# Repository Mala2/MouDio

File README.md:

<p align="center">

	  <br/>
  	<a href="https://discord.gg/jvKunuGb8d">

<p align="center">
🚨 ⚠ This project is currently still under development ⚠️ 🚨

<p align="center">

<p align="center">
(https://www.MouDio.net)
</p>

# Overview
Introducing the fully functional Bluetooth Speaker, featuring modern design and high-performance capabilities. With the choice of ATmega328P or ESP32 microcontroller at its core and compatibility with Arduino & Platformio, this portable speaker offers easy construction, allowing users to quickly and easily set it up, and the high-quality audio ensures that your music will sound great.

The speaker also boasts the Qualcomm® CSR8675 FSC-BT806 and 2x Texas Instruments® TAS5825M amplifiers, providing low distortion and powerful output of 2 x 30 W.

The PCB prototypes have been built and tested, with excellent results. The hardware design is complete, and we are now focusing on the software development. We invite you to explore the shared files for more information on this exciting project.

[*🎨 View on FUSION 360*](https://a360.co/3Bk0sSi)
<p align="center">

# Features
	
* **Amplifier** - 2x  Texas Instruments® [*TAS5825M*](https://www.ti.com/product/TAS5825M) Which has low distortion can output 2x 30 W, 2.2 Mode (8-Ω, 24 V, THD+N=1%)
* **Connectivity** - The [*FSC-BT806 Feasycom*](https://github.com/Mala2/FSC-BT806) features
 Qualcomm® **CSR8675** - **Bluetooth V5.0** Support HSP, HFP, A2DP, AVRCP, PBAP,MAP,SPP,BLE profile - Coverage up to 15m - 2 microphone inputs - **Audio interfaces:** I²S/PCM and SPDIF

* **Power** - Accept **USB C IN** Delivery **Up to 2.5A  Charge Current**  - **USB A OUT** Capable of **10W-5V,2A** - **Low idle power** consumption - **7500mAh** battery capacity upgradeable to **15000mAh**

* **Arduino IDE Programmable Bluetooth-Speaker**
<p align="center">

 # Repository Contents

👩‍🚀 **[3D Files ](3D-Files)** • The **Bluetooth-Speaker** components in many formats (probably what you are looking for to 3d print)

🔉 **[Hardware](Hardware)** • The internal PCBs files (Gerber, Schematic)

💻 **[Software](Software)** • Codes and Libraries for use with the **MouDio**

📄 **[Documentation](Documentation)** • Datasheets, other references

🎲 **[Prototype](Prototype)** • Evaluation board, Cases, etc.

<p align="center">

# Block Diagram

The following displays the latest Block Diagram; Things may change, and probably there may be some discrepancy between the schematic and the block diagram.

<p align="center">

# Schematics

The following displays the ****[TOP Main](Documentation/TOP-Main/)**** PCB. It contain the Atmega328|ESP32 uC, LED Driver, Haptic Driver, RTC, Touch Sensor (TPR54|48), EEPROM*, Supervisory, Addressable LEDs

****[V1](Hardware/TOP/)****
	
[📐 *View on FUSION 360*](https://a360.co/3VPY0L3)

<p align="center">

The following displays the ****[BACK Charger](Documentation/BACK-Charger/)**** PCB.It contain MAX77961 3S Charger, MAX17320 Fuel Gauge, MAX25231ATCA 5V Buck, MAX77503BEWC33 3V3 Buck, 3S Battery.

****[V1](Hardware/BACK/)****
	
[📐 *View on FUSION 360*](https://a360.co/3UELmh8)
	
<p align="center">

The following displays the ****[BOTTOM Amplifier](Documentation/BOTTOM-Amplifier/)**** PCB.It contain the Amplifier - 2x Texas Instruments® TAS5825M and The FSC-BT806 Feasycom Bluetooth Moduel.

****[V1](Hardware/BOTTOM/)****	
	
[📐 *View on FUSION 360*](https://a360.co/3FziKBq)

<p align="center">

The following displays the ****[FRONT Speaker](Documentation/FRONT-Speaker/)**** PCB.To hold the Speakers and front acrylic grill

****[V1](Hardware/FRONT/)****
	
[📐 *View on FUSION 360*](https://a360.co/3BfI0KE)

<p align="center">

# Working Principal

**1. First, I am going to use the TPR54 Touch Sensor Modules to turn ON/OFF the system, if pin [I/O-2] "TAP" it is pressed >2s. This module can send  active High signal output to the ATmega328p pin 2 [INT0].**

**2. After waking up, the ATmega328 will send a high signal to turn on the Bluetooth Module BT-806 through pin [8] "Vreg" and the TAS5825 circuitry through pin [A3] "PDN".**

🔸	**Startup Procedures: [I/O_2] "TAP" pressed for >2s**

*	The ATmega328p wakes up upon High signal on pin 2 [INT0].

*	Send a 3V3 high signal to haptic driver to enable the IC.

*       initialize the LED driver IS31FL3195 to wakeup.

*	Turn on the haptic driver as an indication for 1s.

*	Turn on the LED driver to play a motion from left to right as wake up inication.

*	Turn on the LED driver to reflect the current SOC% of the battery with the help of the fuel gauge MAX17320 and check whether the charger is presnt or not set the LEDs accordingly. 

*	Send a 3V3 high signal of more than 100ms to Bluetooth Module BT-806 through VREG_IN (PLAY/PAUSE) pin to boot the module, then bring the signal back to low.

*	Once power supplies are stable, bring up PDN of TAS5825 to High and wait 5ms.

*	Set the Amplifier TAS5825 into the HiZ state and enable DSP via the I2C control port.

*	Wait 5ms at least. Then initialize the DSP Coefficient, then set the TAS5825 to Play state.

*       initialize the charger MAX77961.

	<br />
	
🔸	**Shutdown Procedures: [I/O_2] "TAP" pressed for >2s**

*	Configure the Register 0x03h -D[1:0]=10 (Hiz) via the I2C control port and Pull PDN low.

*	Wait at least 6ms (this time depends on the LRCLK rate, digital volume, and digital volume ramp-down rate).

*	Send a 3V3 high signal of more than 100ms to Bluetooth Module BT-806 through VREG_IN (PLAY/PAUSE) pin to turn off the module, then bring the signal back to low.

*	The ATmega328 goes to deep sleep, waiting for the next event.
	
	<br />

🔸	**Charging Procedures:**

*	Once the charge input is present, the MAX77961 will send an interrupter either through INTB, INOKB pins

*	Turn on the haptic driver as an indication for 1s.

*	Display the current SOC% with 4 LEDs with the help of an LED driver as long as the charge input is present. Otherwaise, the ATmega328 goes to deep sleep, waiting for the next event.

<br />
	
**3. Once the speaker is ON, the TPR54 is responsible for interacting with Bluetooth Module BT-806 to change the song and volume. (Keep in mind that the TAS5825 can also change just the volume) through TX/RX UART pin between the ATmega328 and Bluetooth Module BT-806 at 115200 rate data. For example: Once the ATmega328 is connected to BT-806, It can send a command to change the volume. For example,**

**And so on. Also, if the BAT SOC% is low, alert the user with an LED blinking and start the Shutdown Procedures once the BAT is too low to operate the system > 15%.**

# To Do List

♦️ **Need help with software part.**

1- After making sure the BT806 is OFF through the commands AT+, Turns the BT806 after turning the 3v3. Sending a high signal to Vreg for > 2s upon waking up, then remain Low. (OR MOSFET NETWORK)
	
2- If the battery is < 15%, shut down the speaker if no charging is present.
			     
✅ 3- If the battery is <35%, set the MAX volume to be less than 70%. In other words, it reduces the volume to not consume more power. TAS5825 has register 0x4c and 0x54 (AGAIN or DIGITAL_VOL) to set that.

4- (after checking the vol range of bt806), send a command AT+SPKVOL and check the volume range of BT806 sent. After that, set the TAS5825 accordingly; that can be done with two registers, either 0x4c and 0x54 (AGAIN or DIGITAL_VOL).
	
✅ 5- For example, once the user swap to the right (Next Song). The LEDs should indicate that from left to right emotions.

6- If no sounds or connection is established for 30 min, turn off the speaker. Either by checking the current flow from the fuel gauge MAX17320 or the BT-806 is not in play status or the TAS5825 register 0x03 is mute status for more than 30 min.

✅ 7- If the charger is inserted, activate the haptic driver as feedback.

9- If the charger is inserted, increase the volume range to be even higher as more power will be provided. This can be done if the 0x4C register is changed accordingly with the attached and disattached of the charger.

10- Add resetFunc() after touching the middle TAP more than 10s.

11- Get the header file for the TAS5825M to act as Dual stereo 2.2 and output the best sounds. You need PPC3 software and hardware access to test the setup and extract the best DSP settings.

12- Create the initialization code configuring the bq28z610 fuel gauge to work with the Arduino Uno and create a Library, and also create a “control” object for the bq28z610 fuel gauge. This includes configuring the IC’s registers via I2C to set configurations. In addition, looking to expose all features of the target ICs in code so that a user can easily configure those features using variables.

♦️ TO BE CONTINUED
	<p align="center">
     
# Components

🔷 **Speakers**

<p align="center">

[*ND65-8 2-1/2"*](https://www.parts-express.com/Dayton-Audio-ND65-8-2-1-2-Aluminum-Cone-Full-Range-Driver-8-290-206?gclid=CjwKCAjwkvWKBhB4EiwA-GHjFrtrRhF_nZh4KP2HR51msc4nOYF4FvnND1y967XQK91w8MbXJw41TxoC_Y0QAvD_BwE) **X2**

🔷 **Tweeters**

<p align="center">

[*ND20FA-6 3/4"*](https://www.parts-express.com/Dayton-Audio-ND20FA-6-3-4-Soft-Dome-Neodymium-Tweeter-275-030?quantity=1&custcol1=Dayton%20Audio%20ND20FA-6%203%2F4%22%20Soft%20Dome%20Neodymium%20Tweeter&custcol_ava_item=275-030&custcol_ava_incomeaccount=General&custcol_ava_upccode=844632000874&custcol_ava_pickup=F&custcol_disableshopping=F) **X2**

🔷 **Acousta-Stuf Polyfill**

<p align="center">

[*Acousta-Stuf Polyfill*](https://www.parts-express.com/Acousta-Stuf-Polyfill-1-lb.-Bag-260-317?quantity=1&custcol1=Acousta-Stuf%20Polyfill%201%20lb.%20Bag&custcol_ava_item=260-317&custcol_ava_incomeaccount=General&custcol_ava_upccode=844632037382&custcol_ava_pickup=F&custcol_disableshopping=F)

🔷 **Brass Threaded Metal**
M3 3mm M3-0.5 Brass Threaded Metal Heat Set Screw Inserts for 3D Printing

<p align="center">

[*Brass Threaded Metal*](https://www.ebay.com/itm/292174792941)

🔷 **Silicone Rubber Mat 60x8x3mm**

<p align="center">

[*Silicone Rubber Mat*](https://www.aliexpress.com/item/3256801841973589.html?spm=a2g0o.order_list.0.0.21ef1802Ng4OPe&gatewayAdapt=4itemAdapt)**X2**

<p align="center">

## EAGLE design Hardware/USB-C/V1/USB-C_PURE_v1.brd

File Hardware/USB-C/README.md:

[📐 *View on FUSION 360*](https://a360.co/3fcBBV4)

FRONT
-------------------

BACK
-------------------

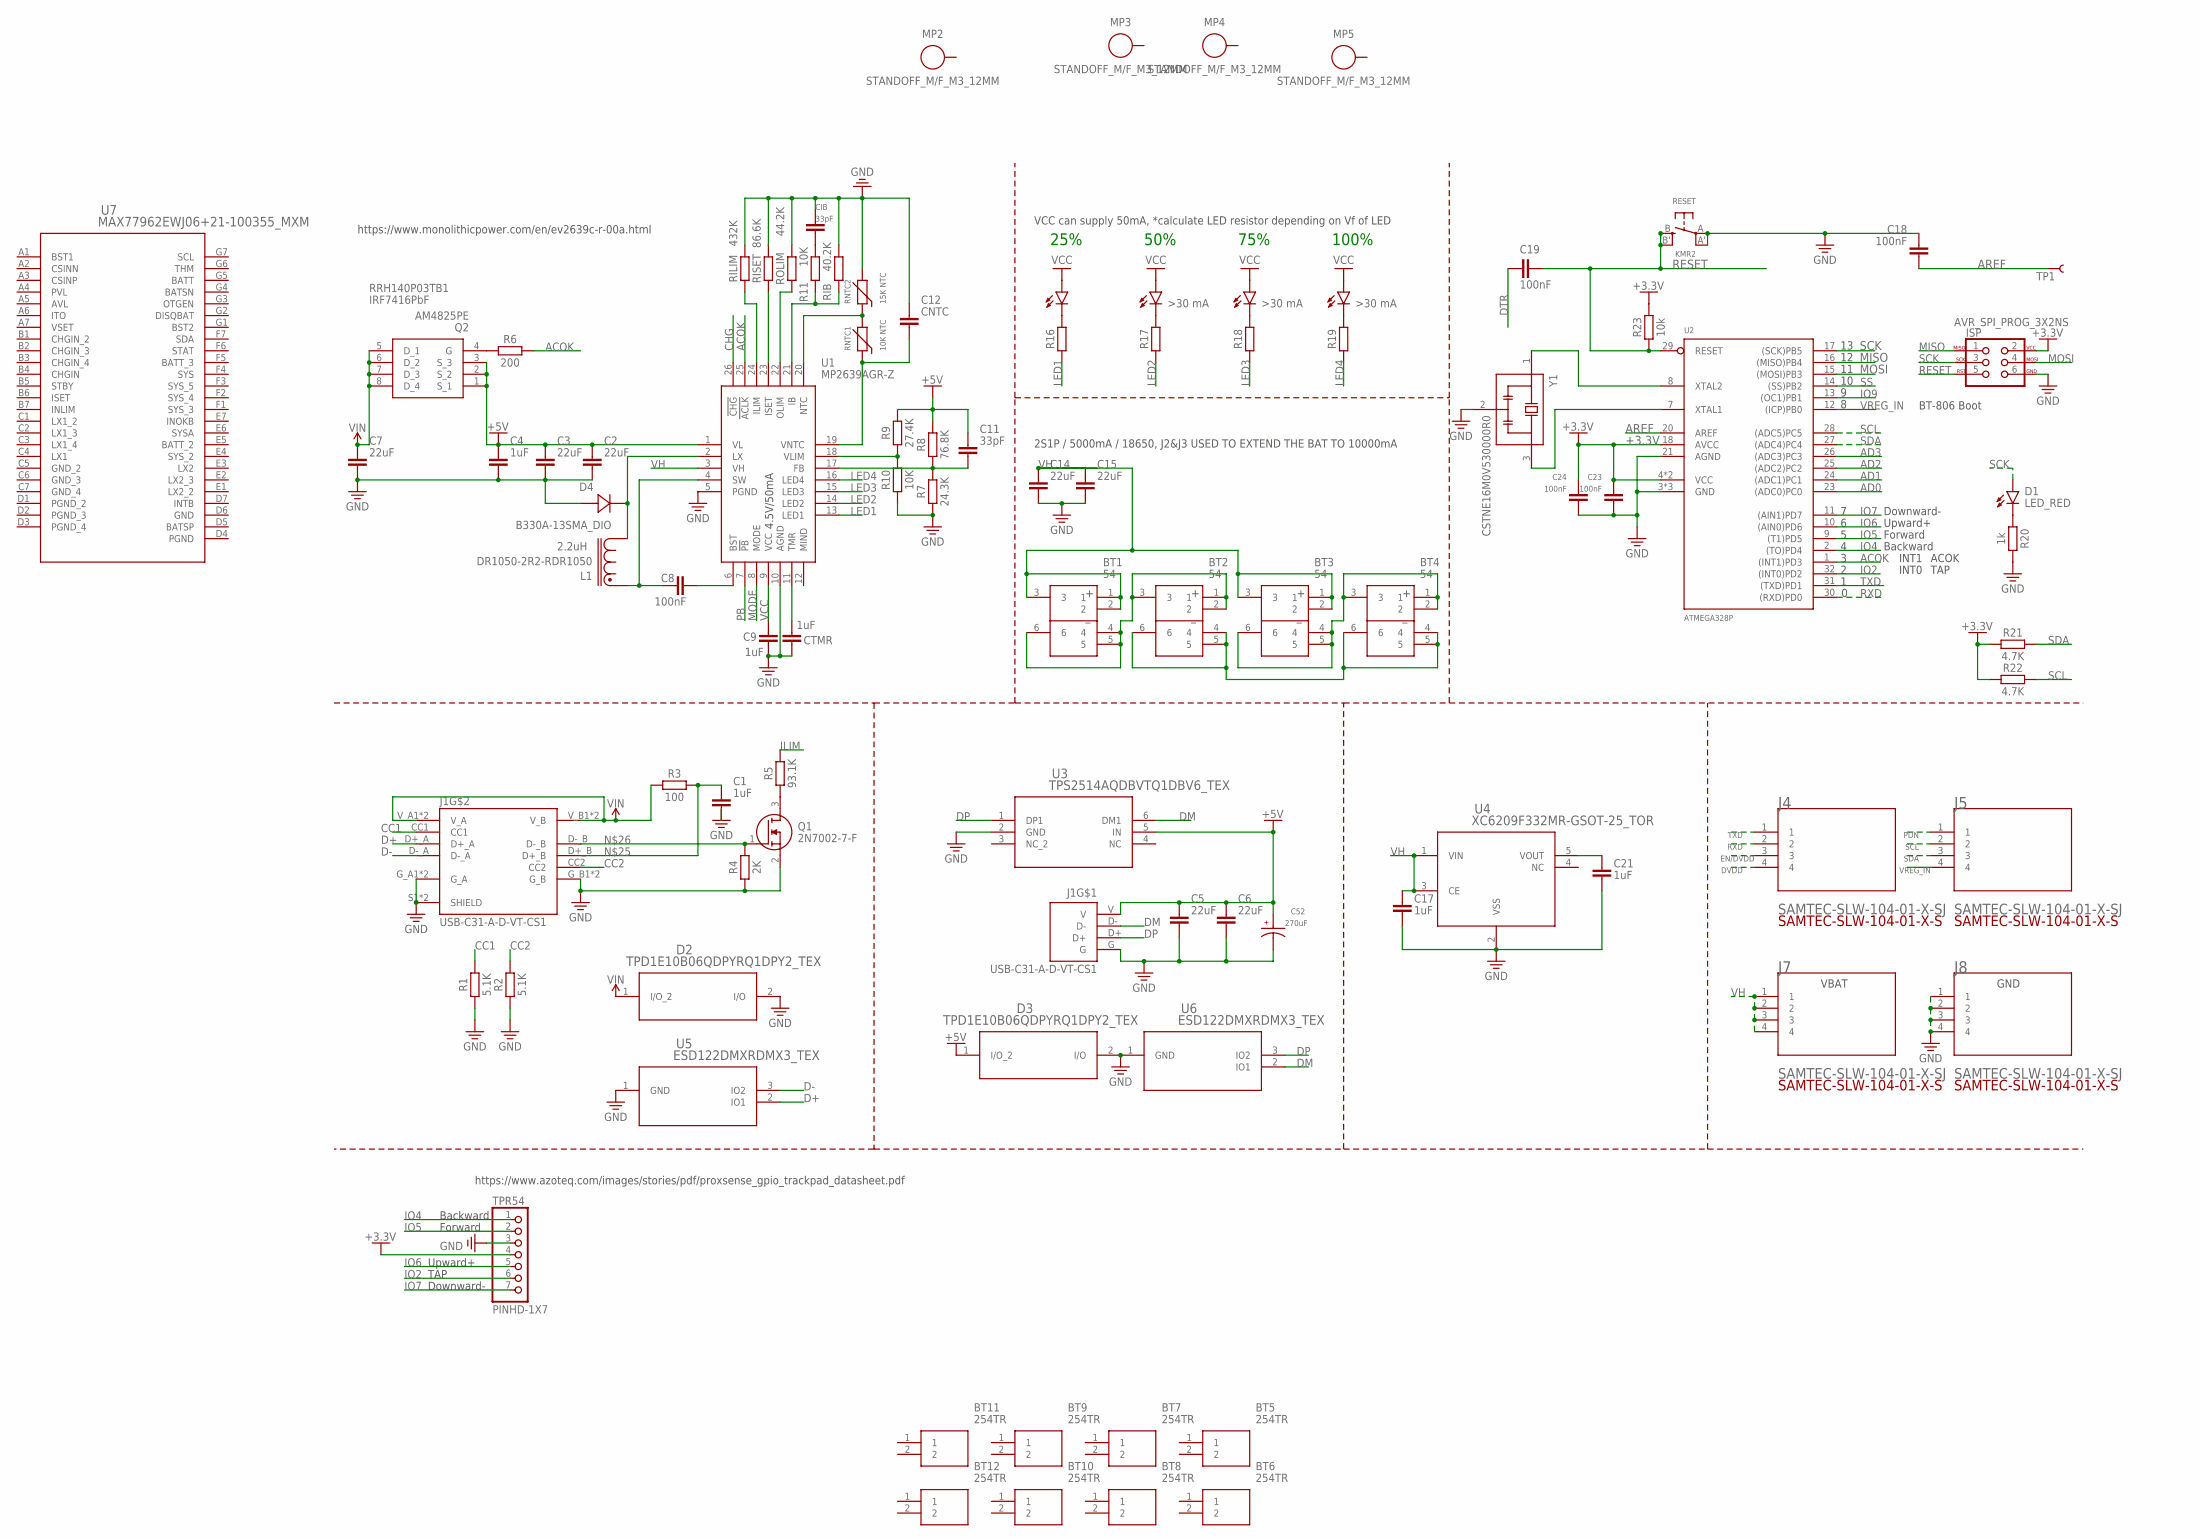
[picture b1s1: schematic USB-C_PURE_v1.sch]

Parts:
BT1, BT2, BT3, BT4: 54
BT5, BT6, BT7, BT8, BT9, BT10, BT11, BT12: 254TR
C1, C4, C9, C17, C21: 1uF; CAPC2012X110
C2, C3, C5, C6, C7, C14, C15: 22uF; CAPC2012X110
C8, C18, C19, C23, C24: 100nF; CAPC1005X60
C11: 33pF; CAPC1005X60
C12: CNTC; CAPC1005X60
C52: 270uF; CAP_16SVPG270M
CIB: 33pF; CAPC1005X60
CTMR: 1uF; CAPC2012X110
D1: LED_RED; LEDC2012X105N_RND-R
D2, D3: TPD1E10B06QDPYRQ1DPY2_TEX; DPY2_TEX
D4: B330A-13SMA_DIO; SMA_DIO
ISP: AVR_SPI_PROG_3X2NS; 2X3-NS
J1: USB-C31-A-D-VT-CS1; ADAMTECH_USB-C31-A-D-VT-CS1
J4, J5, J7, J8: SAMTEC-SLW-104-01-X-SJ; SAMTEC-SLW-104-01-X-S
L1: DR1050-2R2-RDR1050; DR1050
LED1: AA2810
LED2, LED3, LED4: EAPL3809WA1
MP2, MP3, MP4, MP5: STANDOFF_M/F_M3_12MM; STANDOFF_HEX_MALE-FEMALE_550X1200_M3X0.5_MTGP850H320
Q1: 2N7002-7-F; SOT96P240X120-3N
Q2: AM4825PE; SOIC127P600X175-8N
R1, R2: 5.1K; RESC1005X40
R3: 100; RESC1005X40
R4: 2K; RESC1005X40
R5: 93.1K; RESC1005X40
R6: 200; RESC1005X40
R7: 24.3K; RESC1005X40
R8: 76.8K; RESC1005X40
R9: 27.4K; RESC1005X40
R10, R11: 10K; RESC1005X40
R16, R17, R18, R19: R_CHIP-0402(1005-METRIC); RESC1005X40
R20: 1k; RESC1005X40
R21, R22: 4.7K; RESC1005X40
R23: 10k; RESC1005X40
RESET: KMR2; BTN_KMR2_4.6X2.8
RIB: 40.2K; RESC1005X40
RILIM: 432K; RESC1005X40
RISET: 86.6K; RESC1005X40
RNTC1: 10K NTC; THRMC1608X60N
RNTC2: 15K NTC; THRMC1608X60N
ROLIM: 44.2K; RESC1005X40
TP1: TEST-POINT3; PAD.03X.03
TPR54: PINHD-1X7; 1X07
U1: MP2639AGR-Z; MP2639AGRZ
U2: ATMEGA328P; MLF32-TH
U3: TPS2514AQDBVTQ1DBV6_TEX; DBV6_TEX
U4: XC6209F332MR-GSOT-25_TOR; SOT-25_TOR
U5, U6: ESD122DMXRDMX3_TEX; DMX3_TEX
U7: MAX77962EWJ06+21-100355_MXM; 21-100355_MXM
Y1: CSTNE16M0V530000R0; OSC_CSTNE16M0V530000R0

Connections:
+3.3V: C23.1, C24.1, ISP.2, R21.1, R22.1, R23.2, TPR54.4, U2.4 (VCC), U2.6 (VCC), U2.18 (AVCC)
+5V: C2.1, C3.1, C4.1, C5.1, C6.1, C11.1, C52.1, D3.1 (I/O_2), J1.V, Q2.1 (S_1), Q2.2 (S_2), Q2.3 (S_3), R8.2, R9.2, U1.1 (VL), U3.5 (IN)
ACOK: R6.2, U1.25 (!ACLK), U2.1 ((INT1)PD3)
AD0: U2.23 ((ADC0)PC0)
AD1: U2.24 ((ADC1)PC1)
AD2: U2.25 ((ADC2)PC2)
AD3: U2.26 ((ADC3)PC3)
AREF: C18.2, TP1.P$1, U2.20 (AREF)
CC1: J1.CC1, R1.2
CC2: J1.CC2, R2.2
CHG: U1.26 (!CHG)
D+: J1.D+_A, U5.2 (IO1)
D-: J1.D-_A, U5.3 (IO2)
DM: J1.D-, U3.6 (DM1), U6.2 (IO1)
DP: J1.D+, U3.1 (DP1), U6.3 (IO2)
DTR: C19.1
DVDD: J4.4
EN/DVDD: J4.3
GND: C1.2, C2.2, C3.2, C4.2, C5.2, C6.2, C7.2, C9.2, C12.1, C14.2, C15.2, C17.2, C18.1, C21.2, C23.2, C24.2, C52.2, CIB.1, CTMR.1, D2.2 (I/O), D3.2 (I/O), D4.2, ISP.6, J1.G, J1.G_A1 (G_A), J1.G_A2 (G_A), J1.G_B1 (G_B), J1.G_B2 (G_B), J1.S1 (SHIELD), J1.S2 (SHIELD), J8.1, J8.2, J8.3, J8.4, Q1.2 (S), R1.1, R2.1, R4.1, R7.1, R10.1, R20.2, RESET.A, RESET.A' (P1), RIB.2, RILIM.2, RISET.2, RNTC2.2, ROLIM.2, TPR54.3, U1.5 (PGND), U1.10 (AGND), U2.3 (GND), U2.5 (GND), U2.21 (AGND), U2.TH (GND), U3.2 (GND), U4.2 (VSS), U5.1 (GND), U6.1 (GND), U7.D6 (GND), Y1.2 (GND)
GND_2: U7.C5 (GND_2)
GND_3: U7.C6 (GND_3)
GND_4: U7.C7 (GND_4)
ILIM: R5.2
IO2: TPR54.6, U2.32 ((INT0)PD2)
IO4: TPR54.1, U2.2 ((TO)PD4)
IO5: TPR54.2, U2.9 ((T1)PD5)
IO6: TPR54.5, U2.10 ((AIN0)PD6)
IO7: TPR54.7, U2.11 ((AIN1)PD7)
IO9: U2.13 ((OC1)PB1)
LED1: R16.1, U1.13 (LED1)
LED2: R17.1, U1.14 (LED2)
LED3: R18.1, U1.15 (LED3)
LED4: R19.1, U1.16 (LED4)
MISO: ISP.1, U2.16 ((MISO)PB4)
MODE: U1.8 (MODE)
MOSI: ISP.4, U2.15 ((MOSI)PB3)
unnamed: Q2.4 (G), R6.1
unnamed: BT1.4, BT1.5, BT1.6, BT2.1, BT2.2, BT2.3
unnamed: Q1.3 (D), R5.1
unnamed: BT3.4, BT3.5, BT3.6, BT4.1, BT4.2, BT4.3
unnamed: LED2.- (C), R17.2
unnamed: LED1.- (C), R16.2
unnamed: C8.1, L1.1, U1.4 (SW)
unnamed: D4.1, L1.2, U1.2 (LX)
unnamed: C8.2, U1.6 (BST)
unnamed: CTMR.2, U1.11 (TMR)
unnamed: C11.2, R7.2, R8.1, U1.17 (FB)
unnamed: R9.1, R10.2, U1.18 (VLIM)
unnamed: RNTC1.2, RNTC2.1, U1.20 (NTC)
unnamed: C12.2, RNTC1.1, U1.19 (VNTC)
unnamed: RILIM.1, U1.24 (ILIM)
unnamed: RISET.1, U1.23 (ISET)
unnamed: ROLIM.1, U1.22 (OLIM)
unnamed: CIB.2, R11.2
unnamed: R11.1, RIB.1, U1.21 (IB)
unnamed: LED3.- (C), R18.2
unnamed: LED4.- (C), R19.2
unnamed: D1.C, R20.1
unnamed: BT2.4, BT2.5, BT2.6, BT4.4, BT4.5, BT4.6
unnamed: C21.1, U4.5 (VOUT)
unnamed: C1.1, J1.D+_B, R3.2
unnamed: J1.D-_B, Q1.1 (G), R4.2
PB: U1.7 (!PB)
PDN: J5.1
PGND: U7.D4 (PGND)
PGND_2: U7.D1 (PGND_2)
PGND_3: U7.D2 (PGND_3)
PGND_4: U7.D3 (PGND_4)
RESET: C19.2, ISP.5, R23.1, RESET.B (S), RESET.B' (S1), U2.29 (RESET)
RXD: J4.2, U2.30 ((RXD)PD0)
SCK: D1.A, ISP.3, U2.17 ((SCK)PB5)
SCL: J5.2, R22.2, U2.28 ((ADC5)PC5)
SDA: J5.3, R21.2, U2.27 ((ADC4)PC4)
SS: U2.14 ((SS)PB2)
TXD: J4.1, U2.31 ((TXD)PD1)
VCC: C9.1, LED1.+ (A), LED2.+ (A), LED3.+ (A), LED4.+ (A), U1.9 (VCC)
VH: BT1.1, BT1.2, BT1.3, BT3.1, BT3.2, BT3.3, C14.1, C15.1, C17.1, J7.1, J7.2, J7.3, J7.4, U1.3 (VH), U4.1 (VIN), U4.3 (CE)
VIN: C7.1, D2.1 (I/O_2), J1.V_A1 (V_A), J1.V_A2 (V_A), J1.V_B1 (V_B), J1.V_B2 (V_B), Q2.5 (D_1), Q2.6 (D_2), Q2.7 (D_3), Q2.8 (D_4), R3.1
VREG_IN: J5.4, U2.12 ((ICP)PB0)
XTAL1: U2.7 (XTAL1), Y1.3 (OUT)
XTAL2: U2.8 (XTAL2), Y1.1 (IN)

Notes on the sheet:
100%
75%
50%
25%
IRF7416PbF
RRH140P03TB1
2.2uH
https://www.monolithicpower.com/en/ev2639c-r-00a.html
4.5V/50mA
2S1P / 5000mA / 18650, J2&J3 USED TO EXTEND THE BAT TO 10000mA
VCC can supply 50mA, *calculate LED resistor depending on Vf of LED
GND
VBAT
INT1
INT0
https://www.azoteq.com/images/stories/pdf/proxsense_gpio_trackpad_datasheet.pdf
Backward
Upward+
Forward
Downward-
TAP
ACOK
BT-806 Boot

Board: 2 copper layers, 91 parts (44 on the bottom side), 60 nets, no tracks yet.

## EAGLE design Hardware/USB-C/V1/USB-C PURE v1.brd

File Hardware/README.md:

Components
========================================

Speakers
--------------

[*ND65-8 2-1/2"*](https://www.parts-express.com/Dayton-Audio-ND65-8-2-1-2-Aluminum-Cone-Full-Range-Driver-8-290-206?gclid=CjwKCAjwkvWKBhB4EiwA-GHjFrtrRhF_nZh4KP2HR51msc4nOYF4FvnND1y967XQK91w8MbXJw41TxoC_Y0QAvD_BwE) **X2**

OR

[*ND65-4 2-1/2"*](https://www.parts-express.com/Dayton-Audio-ND65-4-2-1-2-Aluminum-Cone-Full-Range-Driver-290-204?quantity=1&custcol1=Dayton%20Audio%20ND65-4%202-1%2F2%22%20Aluminum%20Cone%20Full-Range%20Driver&custcol_ava_item=290-204&custcol_ava_incomeaccount=General&custcol_ava_upccode=844632081460&custcol_ava_pickup=F&custcol_disableshopping=F) **X2**

Tweeters
--------------

[*ND20FA-6 3/4"*](https://www.parts-express.com/Dayton-Audio-ND20FA-6-3-4-Soft-Dome-Neodymium-Tweeter-275-030?quantity=1&custcol1=Dayton%20Audio%20ND20FA-6%203%2F4%22%20Soft%20Dome%20Neodymium%20Tweeter&custcol_ava_item=275-030&custcol_ava_incomeaccount=General&custcol_ava_upccode=844632000874&custcol_ava_pickup=F&custcol_disableshopping=F) **X2**

Chemcast Black LED Acrylic
--------------

[*Chemcast Black LED Acrylic*](https://www.tapplastics.com/product/plastics/cut_to_size_plastic/black_led_sheet/668) **X1** For the front panel done by laser cut

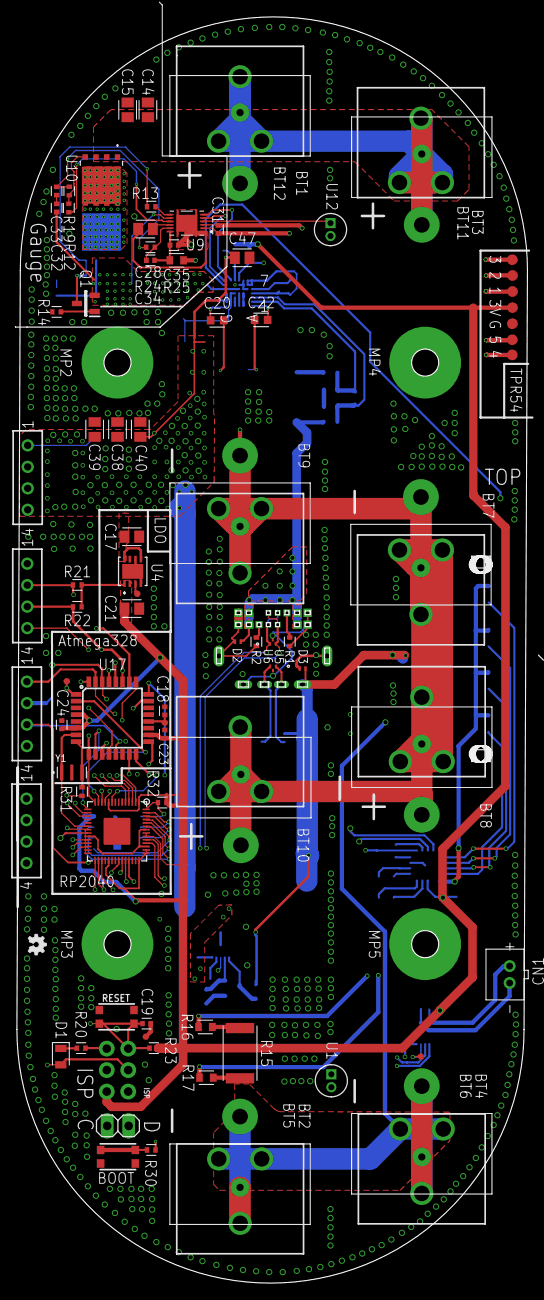
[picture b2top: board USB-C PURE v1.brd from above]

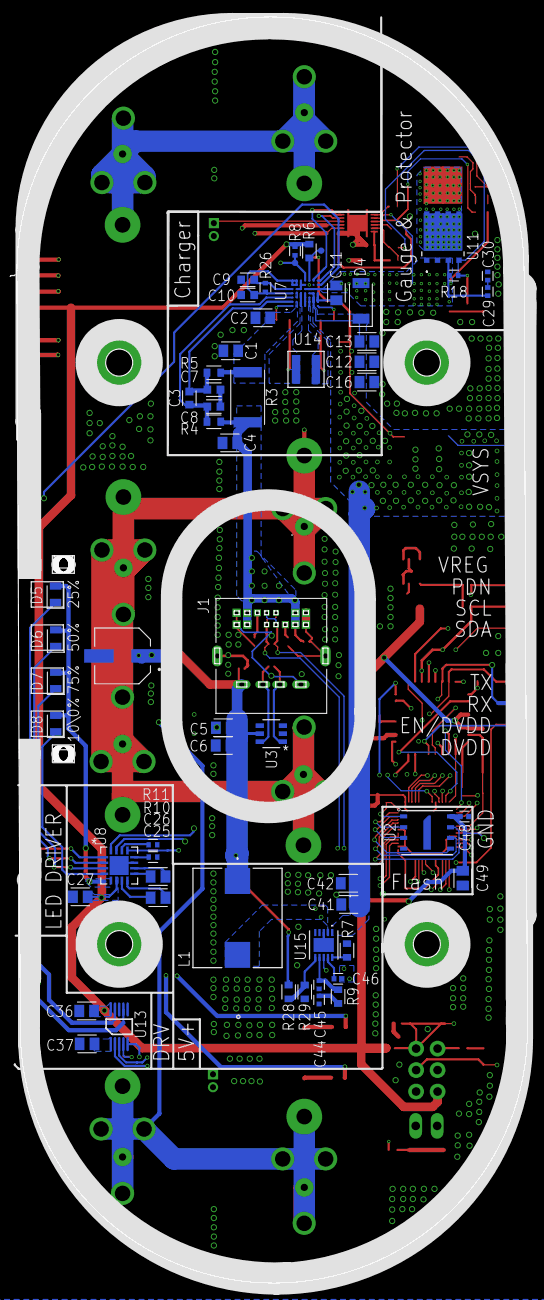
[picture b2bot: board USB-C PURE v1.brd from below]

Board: 4 copper layers, 60.4 x 149.8 mm, 150 parts (60 on the bottom side), 99 nets.

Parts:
BT1, BT2, BT3, BT4: 54
BT5, BT6, BT7, BT8, BT9, BT10, BT11, BT12: 254TR
C1, C2, C4, C5, C6, C11, C12, C13, C14, C15, C16, C17, C21, C38, C39, C40, C41, C42, C47: 22uF; CAPC2012X110
C3: 0.1uF; CAPC1608X85
C7, C8: 0.015uF; CAPC1608X85
C9, C10: 4.7uF; CAPC1608X85
C18, C19, C23, C24, C29, C30, C31, C32, C33, C35, C46, C48: 100nF; CAPC1005X60
C20, C22: 0.22uF; CAPC1608X85
C25, C26, C27, C36, C37, C49: 1uF; CAPC2012X110
C28: 2.2uF; CAPC2012X110
C34: 1uF; CAPC1005X60
C43: 16SVPG270M; CAP_16SVPG270M
C44: 12nF; CAPC1005X60
C45: 120pF; CAPC1005X60
CN1: JST-PH-2-THM
D1, D5, D6, D7, D8: LED_RED; LEDC2012X105N_RND-R
D2, D3: TPD1E10B06QDPYRQ1DPY2_TEX; DPY2_TEX
D4: PMEG4050ETP,115; SODFL4725X110
IC1: RP2040_QFN56; QFN56_7MM_REDUCEDEPAD
ISP: AVR_SPI_PROG_3X2NS; 2X3-NS
J1: USB-C31-A-D-VT-CS1; ADAMTECH_USB-C31-A-D-VT-CS1
J4, J5, J7, J8: SAMTEC-SLW-104-01-X-SJ; SAMTEC-SLW-104-01-X-S
JP1: PINHD-1X2; 1X02
L1: 15uH; IND_IHLP_4040_DZ_VIS
MP2, MP3, MP4, MP5: STANDOFF_M/F_M3_12MM; STANDOFF_HEX_MALE-FEMALE_550X1200_M3X0.5_MTGP850H320
Q1: 2N7002K-T1; SOT96P240X120-3N
R1, R2, R12, R13: 5.1K; RESC1005X40
R3: 0.01; RESC6332X71
R4, R5: 10; RESC1608X60
R6: 200K; RESC1608X60
R7: 143K; RESC1608X60
R8, R21, R22: 4.7K; RESC1005X40
R9: 3.65k; RESC1608X60
R10: 12k; RESC1005X40
R11, R14, R23, R32: 10k; RESC1005X40
R15: 0.001; RESC6332X71
R16, R17, R25: 100; RESC1608X60
R18, R19: 10M; RESC1005X40
R20, R30, R31: 1k; RESC1005X40
R24, R26: 5; RESC1005X40
R28, R29: 100K; RESC1608X60
RESET, RESET1: KMR2; BTN_KMR2_4.6X2.8
TP1, TP2, TP3, TP11, TP12, TP13, TP14: TEST-POINT3; PAD.03X.03
TP4, TP5, TP6, TP7, TP8, TP9, TP10: TEST-POINT3X5; PAD.03X.05
U1, U12: AC103E2FAC_USS; AC_USS
U2: W25QXX128MBIT; WSON-8-6X5-SKINNY_CENTERPAD
U3: TPS2514AQDBVTQ1DBV6_TEX; DBV6_TEX
U4: TLV76633; VSON_DRBRQ1_TEX
U5, U6: ESD122DMXRDMX3_TEX; DMX3_TEX
U7: MAX77962EWJ06+21-100355_MXM; 21-100355_MXM
U8: IS31FL3195QFN-16_UF_LIT-L; QFN-16_UF_LIT-L
U9: BQ28Z610DRZR; IC_BQ27441DRZR-G1A
U10, U11: CSD16412Q5ADQJ8; DQJ8
U13: DRV2605LDGSRDGS0010A; DGS0010A
U14: XAL4030-472MECXAL4030-472MEC_COC; XAL4030-472MEC_COC
U15: TPS54335-1ADRCTDRC10_1P65X2P40_TEX; DRC10_1P65X2P40_TEX
U17: ATMEGA328P_TQFP; TQFP32-08
U$1: OSHW-LOGOMINI; OSHW-LOGO-MINI
U$3: RLP4-200-500; RLP4-200-500_V1
Y1: CSTNE16M0V530000R0; OSC_CSTNE16M0V530000R0

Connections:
1.2V: IC1.23, IC1.45, IC1.50
+3.3V: C21.1, C23.1, C24.1, C27.2, C36.1, C48.2, C49.1, IC1.1, IC1.10, IC1.22, IC1.33, IC1.42, IC1.43, IC1.44, IC1.48, IC1.49, ISP.2, R6.2, R8.2, R21.1, R22.1, R23.2, R32.1, TP7.P$1, U2.8, U4.1, U4.2, U8.6, U13.10, U17.4, U17.6, U17.18
+5V: C5.1, C6.1, C43.1, D3.1, J1.V, L1.1, R28.1, U3.5
AREF: C18.2, TP1.P$1, U17.20
AVL: C9.1, R26.1, U7.A5
BAT+: BT1.1, BT1.2, BT1.3, BT3.1, BT3.2, BT3.3, BT11.1, BT11.2, BT12.1, BT12.2, C14.1, C15.1, U10.1, U10.2, U10.3
BATSN: C11.2, U7.G2, U7.G3, U7.G4
BOOT: R30.2, RESET1.B, RESET1.B'
CC1: J1.CC1, R1.2
CC2: J1.CC2, R2.2
CHG: R12.2, R19.1, U10.4
CSINN: C3.2, C7.1, R5.1, U7.A2
CSINP: C3.1, C8.1, R4.1, U7.A3
D+: IC1.47, J1.D+_A, J1.D+_B, U5.2
D-: IC1.46, J1.D-_A, J1.D-_B, U5.3
DM: J1.D-, U3.6, U6.2
DP: J1.D+, U3.1, U6.3
DSG: Q1.3, R13.2, R18.1, U11.4
DTR: C19.1, TP11.P$1
EN/DVDD: IC1.39, J4.3, U17.13
EN_5V: IC1.37, U15.8, U17.25
EN_HAP: IC1.9, U13.5, U17.23
EN_LED: IC1.36, U8.13, U17.24
GAUGE: BT2.4, BT2.5, BT2.6, BT4.4, BT4.5, BT4.6, BT5.1, BT5.2, BT6.1, BT6.2, C28.1, C35.1, R15.2, R17.1, U9.1, U9.13, U12.2
GND: C1.2, C2.2, C4.2, C5.2, C6.2, C7.2, C8.2, C9.2, C10.2, C12.2, C13.2, C14.2, C15.2, C16.2, C17.2, C18.1, C21.2, C23.2, C24.2, C27.1, C30.1, C36.2, C37.2, C38.2, C39.2, C40.2, C41.2, C42.2, C43.2, C44.2, C45.2, C47.2, C48.1, C49.2, D2.2, D3.2, IC1.P$1, ISP.6, J1.G, J1.G_A1, J1.G_A2, J1.G_B1, J1.G_B2, J1.S1, J1.S2, J7.1, J7.2, J7.3, J7.4, R1.1, R2.1, R7.1, R10.1, R11.1, R14.1, R15.1, R16.1, R20.2, R29.2, RESET.A, RESET.A', RESET1.A, RESET1.A', TP8.P$1, U1.2, U2.4, U3.2, U4.4, U4.6, U4.9, U5.1, U6.1, U7.B5, U7.C5, U7.C6, U7.C7, U7.D1, U7.D2, U7.D3, U7.D4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
INOKB: R6.1, TP13.P$1, U7.E7
INTB: IC1.12, R8.1, TP3.P$1, TP14.P$1, U7.D7, U17.1
IO2: IC1.11, TP5.P$1, U17.32
IO4: IC1.13, TP10.P$1, U17.2
IO5: IC1.14, TP9.P$1, U17.9
IO6: IC1.15, TP6.P$1, U17.10
IO7: IC1.16, TP4.P$1, U17.11
LX1: C22.1, U7.C1, U7.C2, U7.C3, U7.C4, U14.1
LX2: C20.2, U7.E1, U7.E2, U7.E3, U14.2
MID: BT1.4, BT1.5, BT1.6, BT2.1, BT2.2, BT2.3, BT3.4, BT3.5, BT3.6, BT4.1, BT4.2, BT4.3, BT7.1, BT7.2, BT8.1, BT8.2, BT9.1, BT9.2, BT10.1, BT10.2, R25.1
MISO: IC1.31, ISP.1, U17.16
MOSI: IC1.30, ISP.4, U17.15
unnamed: C1.1, C2.1, R3.2, R5.2, U7.B1, U7.B2, U7.B3, U7.B4
unnamed: C28.2, U9.10
unnamed: R7.2, U15.10
unnamed: U9.4, U12.1
unnamed: C26.1, U8.9
unnamed: R10.2, U8.12
unnamed: C46.1, U15.9
unnamed: C20.1, U7.G1
unnamed: C22.2, U7.A1
unnamed: U1.1, U7.G6
unnamed: D5.C, U8.1
unnamed: D6.C, U8.2
unnamed: D7.C, U8.3
unnamed: D8.C, U8.4
unnamed: D5.A, D6.A, D7.A, D8.A, U8.5
unnamed: R11.2, U8.14
unnamed: C25.1, U8.7
unnamed: C25.2, U8.8
unnamed: R12.1, U9.9
unnamed: R13.1, U9.7
unnamed: C29.1, C30.2
unnamed: D1.C, R20.1
unnamed: Q1.1, R14.2
unnamed: TP2.P$1, U13.4
unnamed: C26.2, U8.10
unnamed: C32.2, C33.1
unnamed: U10.5, U10.6, U10.7, U10.8, U11.5, U11.6, U11.7, U11.8
unnamed: C33.2, R19.2, R24.2
unnamed: CN1.2, U13.7
unnamed: CN1.1, U13.9
unnamed: C37.1, U13.1
unnamed: C44.1, R9.2
unnamed: C45.1, R9.1, U15.7
unnamed: TP12.P$1, U4.3
unnamed: R28.2, R29.1, U15.6
PACK+: C11.1, C29.2, C32.1, D4.2, Q1.2, R18.2, U7.D5, U7.E5, U7.F5, U7.G5, U9.8, U11.1, U11.2, U11.3
PDN: IC1.38, J5.1, U17.26
PH: C46.2, L1.2, U15.2
PVL: C10.1, R26.2, U7.A4, U7.A6, U7.A7, U7.B6, U7.B7
QSPI_CS: IC1.56, R30.1, R32.2, U2.1
QSPI_DATA[0]: IC1.53, U2.5
QSPI_DATA[1]: IC1.55, U2.2
QSPI_DATA[2]: IC1.54, U2.3
QSPI_DATA[3]: IC1.51, U2.7
QSPI_SCK: IC1.52, U2.6
RESET: C19.2, IC1.26, ISP.5, R23.1, RESET.B, RESET.B', U17.29
RXD: IC1.3, J4.2, U17.30
SCK: D1.A, IC1.29, ISP.3, U17.17
SCL: IC1.5, J5.2, R22.2, U7.G7, U8.16, U9.5, U13.2, U17.28
SDA: IC1.4, J5.3, R21.2, U7.F7, U8.15, U9.6, U13.3, U17.27
SRN: C31.1, R16.2, U9.2
SRP: C31.2, R17.2, U9.3
SWCLK: IC1.24, JP1.1
SWDIO: IC1.25, JP1.2
TXD: IC1.2, J4.1, U17.31
VC1: C34.1, C35.2, R25.2, U9.12
VC2: C34.2, R24.1, U9.11
VIN: C4.1, D2.1, J1.V_A1, J1.V_A2, J1.V_B1, J1.V_B2, R3.1, R4.2
VREG_IN: IC1.17, J5.4, U17.12
VSYS: C12.1, C13.1, C16.1, C17.1, C38.1, C39.1, C40.1, C41.1, C42.1, C47.1, D4.1, J8.1, J8.2, J8.3, J8.4, U4.5, U4.8, U7.E4, U7.E6, U7.F1, U7.F2, U7.F3, U7.F4, U15.1
XTAL1: IC1.21, R31.1, R31.2, U17.8, Y1.3
XTAL2: IC1.20, U17.7, Y1.1

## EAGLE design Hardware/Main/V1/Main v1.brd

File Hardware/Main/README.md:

[📐 *View on FUSION 360*](https://a360.co/3FjaXoa) 

<p align="center">

FRONT
-------------------

BACK
-------------------

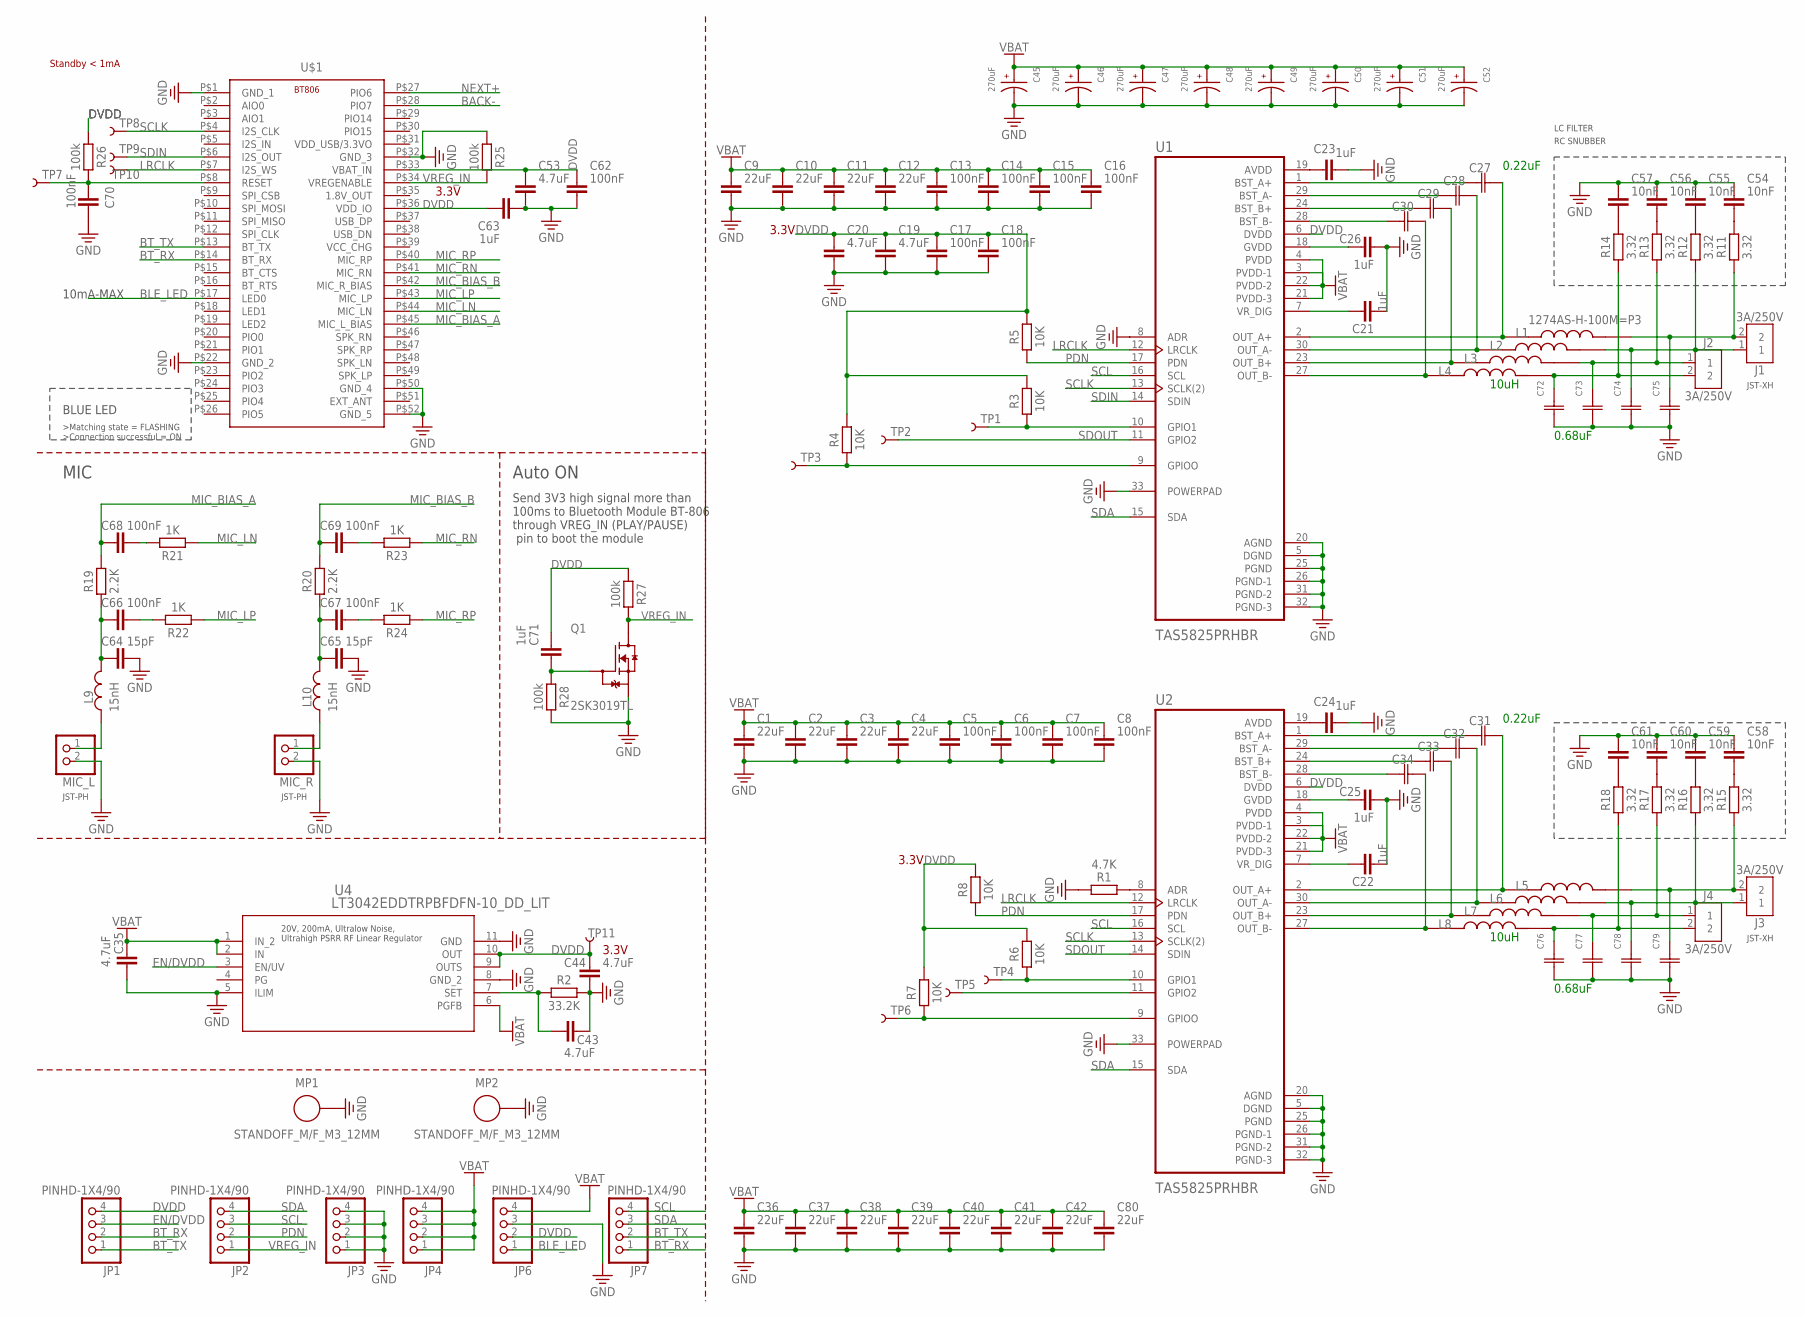
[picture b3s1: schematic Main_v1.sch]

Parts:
C1, C2, C3, C4, C9, C10, C11, C12, C36, C37, C38, C39, C40, C41, C42, C80: 22uF; CAPC2012X110
C5, C6, C7, C8, C13, C14, C15, C16, C17, C18, C62: 100nF; CAPC2012X110
C19, C20: 4.7uF; CAPC3216X135
C21, C22, C23, C24, C25, C26, C63, C71: 1uF; CAPC2012X110
C27, C28, C29, C30, C31, C32, C33, C34: 0.22uF; CAPM7.2X7.2_5_1_VIS
C35, C43, C44, C53: 4.7uF; CAPC2012X110
C45, C46, C47, C48, C49, C50, C51, C52: 270uF; CAP_16SVPG270M
C54, C55, C56, C57, C58, C59, C60, C61: 10nF; CAPC2012X110
C64, C65: 15pF; CAPC1005X60
C66, C67, C68, C69, C70: 100nF; CAPC1005X60
C72, C73, C74, C75, C76, C77, C78, C79: MMK5684J63J03L16.5TR18CAPM7.2X4.5_5_VIS; CAPM7.2X4.5_5_VIS
J1, J2, J3, J4: 3A/250V; B2B-XH-A
JP1, JP2, JP3, JP4, JP6, JP7: PINHD-1X4/90; 1X04/90
L1, L2, L3, L4, L5, L6, L7, L8: 1274AS-H-100M=P3; IND_1274AS-H-100M=P3
L9, L10: 15nH; INDC1006X60N
MIC_L: JST_2PIN-THM; JST-PH-2-THM
MIC_R: JST_2PIN-THM; JST-PH-2-THM
MP1, MP2: STANDOFF_M/F_M3_12MM; STANDOFF_HEX_MALE-FEMALE_550X1200_M3X0.5_MTGP850H320
Q1: 2SK3019TL; TRANS_2SK3019TL
R1: 4.7K; RESC1005X40
R2: 33.2K; RESC1005X40
R3, R4, R5, R6, R7, R8: 10K; RESC1005X40
R11, R12, R13, R14, R15, R16, R17, R18: 3.32; RESC1005X40
R19, R20: 2.2K; RESC1005X40
R21, R22, R23, R24: 1K; RESC1005X40
R25, R26, R27, R28: 100k; RESC1005X40
TP1, TP2, TP3, TP4, TP5, TP6, TP7: TEST-POINT3; PAD.03X.03
TP8, TP9, TP10, TP11: TEST-POINT3X5; PAD.03X.05
U1, U2: TAS5825PRHBR; IC_ADS125H01IRHBT
U4: LT3042EDDTRPBFDFN-10_DD_LIT; DFN-10_DD_LIT
U$1: BT806

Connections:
BACK-: U$1.P$28 (PIO7)
BLE_LED: JP6.1, U$1.P$17 (LED0)
BT_RX: JP1.2, JP7.1, U$1.P$14 (BT_RX)
BT_TX: JP1.1, JP7.2, U$1.P$13 (BT_TX)
DVDD: C17.1, C18.1, C19.1, C20.1, C44.2, C53.1, C62.1, C63.1, C71.1, JP1.4, JP6.2, R3.2, R4.2, R5.2, R6.2, R7.2, R8.2, R26.1, R27.1, TP11.P$1, U1.6 (DVDD), U2.6 (DVDD), U4.9 (OUTS), U4.10 (OUT), U$1.P$33 (VBAT_IN), U$1.P$36 (VDD_IO)
EN/DVDD: JP1.3, U4.3 (EN/UV)
GND: C1.2, C2.2, C3.2, C4.2, C5.2, C6.2, C7.2, C8.2, C9.2, C10.2, C11.2, C12.2, C13.2, C14.2, C15.2, C16.2, C17.2, C18.2, C19.2, C20.2, C21.2, C22.2, C23.2, C24.2, C25.2, C26.2, C35.1, C36.2, C37.2, C38.2, C39.2, C40.2, C41.2, C42.2, C43.2, C44.1, C45.2, C46.2, C47.2, C48.2, C49.2, C50.2, C51.2, C52.2, C53.2, C54.1, C55.1, C56.1, C57.1, C58.1, C59.1, C60.1, C61.1, C62.2, C63.2, C64.2, C65.2, C70.1, C72.1, C73.1, C74.1, C75.1, C76.1, C77.1, C78.1, C79.1, C80.2, JP3.1, JP3.2, JP3.3, JP3.4, JP6.3, MIC_L.2 (1), MIC_R.2 (1), MP1.1, MP2.1, Q1.1 (S), R1.1, R2.2, R25.1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
LRCLK: TP10.P$1, U1.12 (LRCLK), U2.12 (LRCLK), U$1.P$7 (I2S_WS)
MIC_BIAS_A: C68.1, R19.2, U$1.P$45 (MIC_L_BIAS)
MIC_BIAS_B: C69.1, R20.2, U$1.P$42 (MIC_R_BIAS)
MIC_LN: R21.1, U$1.P$44 (MIC_LN)
MIC_LP: R22.1, U$1.P$43 (MIC_LP)
MIC_RN: R23.1, U$1.P$41 (MIC_RN)
MIC_RP: R24.1, U$1.P$40 (MIC_RP)
unnamed: R1.2, U2.8 (ADR)
unnamed: C24.1, U2.19 (AVDD)
unnamed: C23.1, U1.19 (AVDD)
unnamed: C26.1, U1.18 (GVDD)
unnamed: C21.1, U1.7 (VR_DIG)
unnamed: C25.1, U2.18 (GVDD)
unnamed: C22.1, U2.7 (VR_DIG)
unnamed: C27.1, U1.1 (BST_A+)
unnamed: C28.1, U1.29 (BST_A-)
unnamed: C29.1, U1.24 (BST_B+)
unnamed: C30.1, U1.28 (BST_B-)
unnamed: C31.1, U2.1 (BST_A+)
unnamed: C32.1, U2.29 (BST_A-)
unnamed: C33.1, U2.24 (BST_B+)
unnamed: C34.1, U2.28 (BST_B-)
unnamed: C27.2, L1.1, U1.2 (OUT_A+)
unnamed: C28.2, L2.1, U1.30 (OUT_A-)
unnamed: C29.2, L3.1, U1.23 (OUT_B+)
unnamed: C30.2, L4.1, U1.27 (OUT_B-)
unnamed: C31.2, L5.1, U2.2 (OUT_A+)
unnamed: C32.2, L6.1, U2.30 (OUT_A-)
unnamed: C33.2, L7.1, U2.23 (OUT_B+)
unnamed: C34.2, L8.1, U2.27 (OUT_B-)
unnamed: C77.2, J4.1, L7.2, R17.1
unnamed: C78.2, J3.1, L6.2, R16.1
unnamed: C79.2, J3.2, L5.2, R15.1
unnamed: C72.2, J2.2, L4.2, R14.1
unnamed: C75.2, J1.2, L1.2, R11.1
unnamed: C76.2, J4.2, L8.2, R18.1
unnamed: C74.2, J1.1, L2.2, R12.1
unnamed: C73.2, J2.1, L3.2, R13.1
unnamed: C43.1, R2.1, U4.7 (SET)
unnamed: R3.1, TP1.P$1, U1.10 (GPIO1)
unnamed: R6.1, TP4.P$1, U2.10 (GPIO1)
unnamed: R4.1, TP3.P$1, U1.9 (GPIOO)
unnamed: TP5.P$1, U2.11 (GPIO2)
unnamed: R7.1, TP6.P$1, U2.9 (GPIOO)
unnamed: C54.2, R11.2
unnamed: C55.2, R12.2
unnamed: C56.2, R13.2
unnamed: C57.2, R14.2
unnamed: C58.2, R15.2
unnamed: C59.2, R16.2
unnamed: C60.2, R17.2
unnamed: C61.2, R18.2
unnamed: L9.1, MIC_L.1 (2)
unnamed: L10.1, MIC_R.1 (2)
unnamed: C64.1, C66.1, L9.2, R19.1
unnamed: C70.2, R26.2, TP7.P$1, U$1.P$8 (RESET)
unnamed: C66.2, R22.2
unnamed: C69.2, R23.2
unnamed: C67.2, R24.2
unnamed: C68.2, R21.2
unnamed: C71.2, Q1.2 (G), R28.1
unnamed: C65.1, C67.1, L10.2, R20.1
NEXT+: U$1.P$27 (PIO6)
PDN: JP2.2, R5.1, R8.1, U1.17 (PDN), U2.17 (PDN)
PG: U4.4 (PG)
SCL: JP2.3, JP7.4, U1.16 (SCL), U2.16 (SCL)
SCLK: TP8.P$1, U1.13 (SCLK(2)), U2.13 (SCLK(2)), U$1.P$4 (I2S_CLK)
SDA: JP2.4, JP7.3, U1.15 (SDA), U2.15 (SDA)
SDIN: TP9.P$1, U1.14 (SDIN), U$1.P$6 (I2S_OUT)
SDOUT: TP2.P$1, U1.11 (GPIO2), U2.14 (SDIN)
VCC: C1.1, C2.1, C3.1, C4.1, C5.1, C6.1, C7.1, C8.1, C9.1, C10.1, C11.1, C12.1, C13.1, C14.1, C15.1, C16.1, C35.2, C36.1, C37.1, C38.1, C39.1, C40.1, C41.1, C42.1, C45.1, C46.1, C47.1, C48.1, C49.1, C50.1, C51.1, C52.1, C80.1, JP4.1, JP4.2, JP4.3, JP4.4, JP6.4, U1.3 (PVDD-1), U1.4 (PVDD), U1.21 (PVDD-3), U1.22 (PVDD-2), U2.3 (PVDD-1), U2.4 (PVDD), U2.21 (PVDD-3), U2.22 (PVDD-2), U4.1 (IN_2), U4.2 (IN), U4.6 (PGFB)
VREG_IN: JP2.1, Q1.3 (D), R25.2, R27.2, U$1.P$34 (VREGENABLE)

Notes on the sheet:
0.22uF
10uH
0.68uF
3.3V
MIC
10mA-MAX
Auto ON
Send 3V3 high signal more than 100ms to Bluetooth Module BT-806 through VREG_IN (PLAY/PAUSE) pin to boot the module
BLUE LED
20V, 200mA, Ultralow Noise, Ultrahigh PSRR RF Linear Regulator
JST-PH
JST-XH
RC SNUBBER
LC FILTER
Standby < 1mA

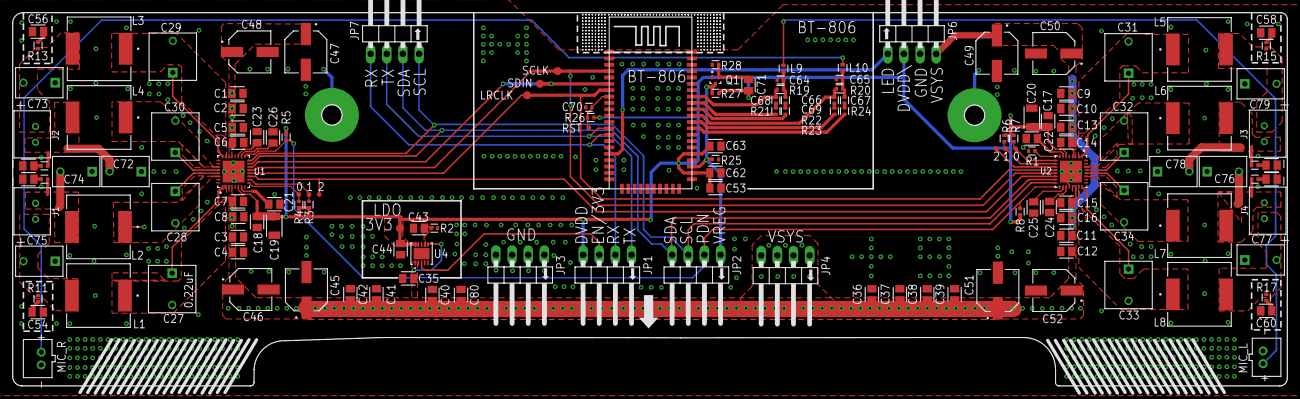
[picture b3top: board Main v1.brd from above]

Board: 2 copper layers, 200.4 x 58.7 mm, 146 parts (0 on the bottom side), 76 nets.

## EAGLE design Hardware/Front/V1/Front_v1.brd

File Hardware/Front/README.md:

[📐 *View on FUSION 360*](https://a360.co/3FjaXoa)

<p align="center">

FRONT
-------------------

BACK
-------------------

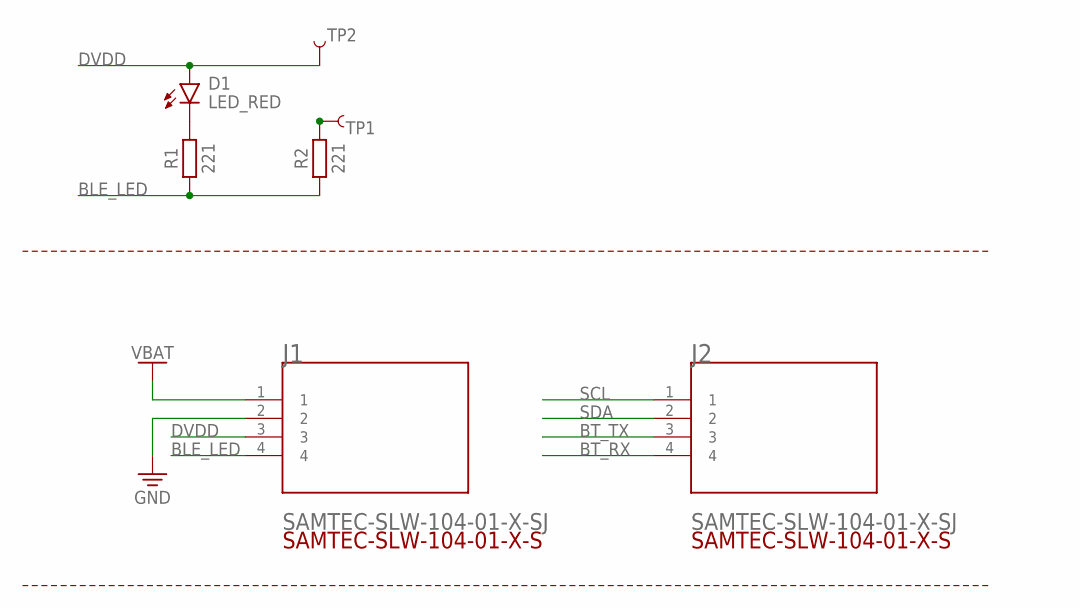
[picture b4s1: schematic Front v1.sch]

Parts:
D1: LED_RED; LEDC1608X65N_RND-R
J1, J2: SAMTEC-SLW-104-01-X-SJ; SAMTEC-SLW-104-01-X-S
R1, R2: 221; RESC1608X60
TP1, TP2: TEST-POINT3X5; PAD.03X.05

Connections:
BLE_LED: J1.4, R1.1, R2.1
BT_RX: J2.4
BT_TX: J2.3
DVDD: D1.A, J1.3, TP2.P$1
GND: J1.2
unnamed: R2.2, TP1.P$1
unnamed: D1.C, R1.2
SCL: J2.1
SDA: J2.2
VCC: J1.1

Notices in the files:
README.md:
License: MIT
parts and their libraries:
SparkFun-Connectors: Licensing: Creative Commons ShareAlike 4.0 International - https://creativecommons.org/licenses/by-sa/4.0
COPYRIGHT: Copyright (C) 2021 Ultra Librarian. All rights reserved.
COPYRIGHT: Copyright (C) 2022 Ultra Librarian. All rights reserved.
